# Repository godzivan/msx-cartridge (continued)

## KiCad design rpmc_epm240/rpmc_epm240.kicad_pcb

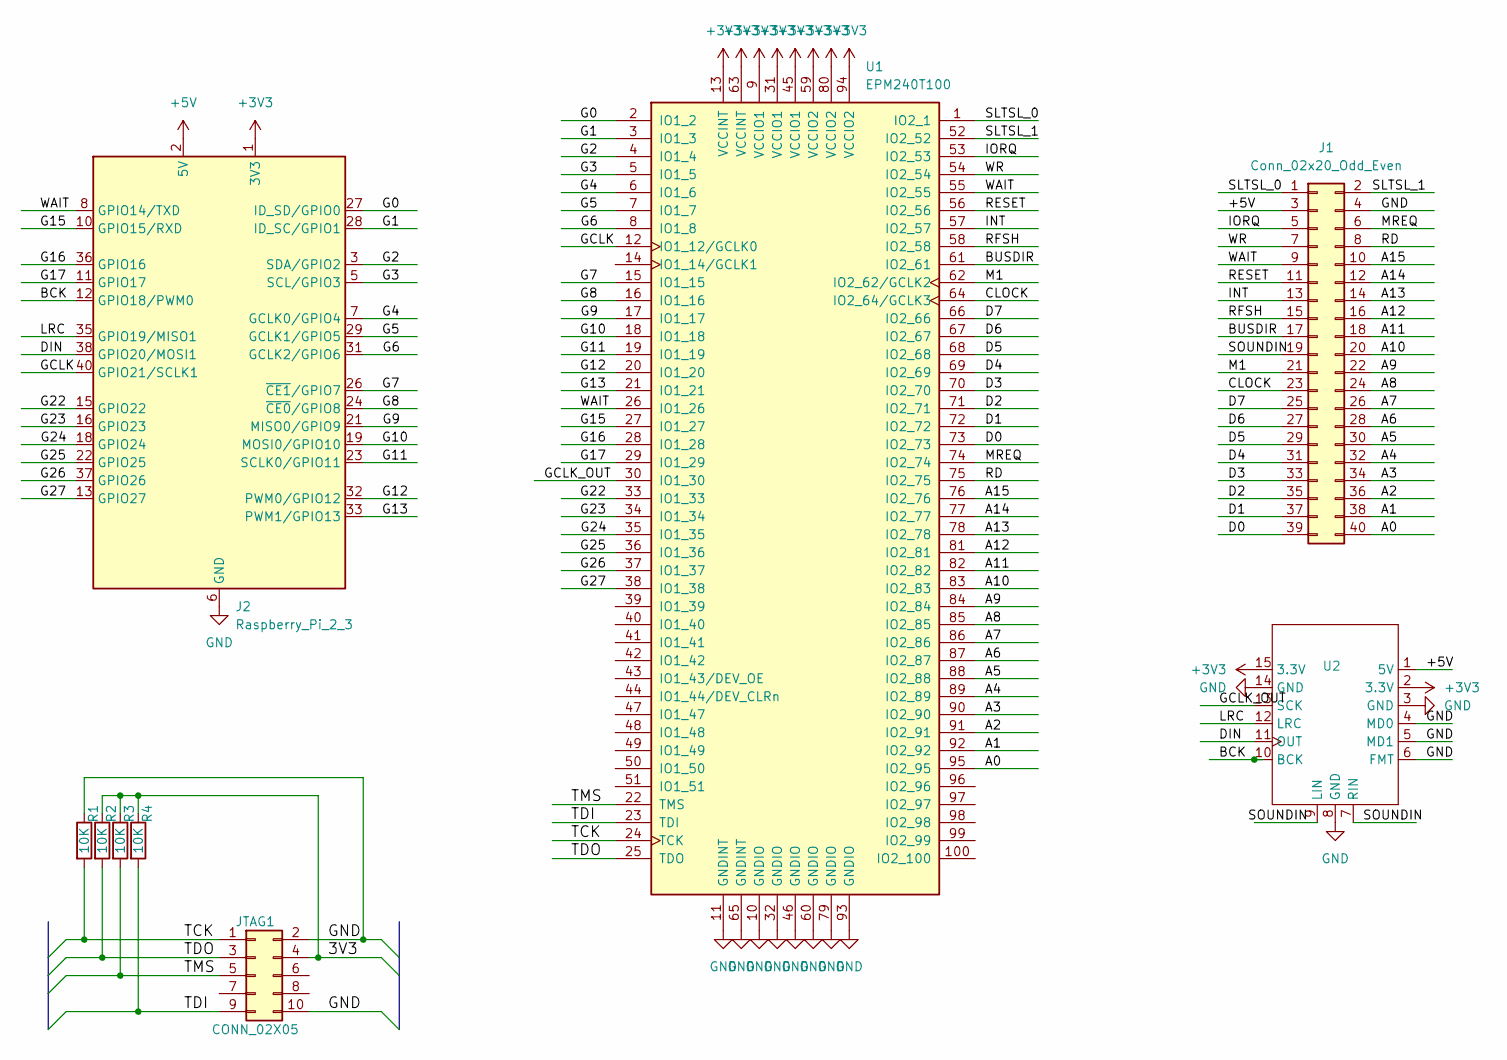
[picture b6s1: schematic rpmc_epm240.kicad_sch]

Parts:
J1: Conn_02x20_Odd_Even; PinHeader_2x20_P2.54mm_Vertical
J2: Raspberry_Pi_2_3; PinHeader_2x20_P2.54mm_Vertical
JTAG1: CONN_02X05; PinHeader_2x05_P2.54mm_Vertical
R1, R2, R3, R4: 10K; R_0201_0603Metric_Pad0.64x0.40mm_HandSolder
U1: EPM240T100; LQFP-100_14x14mm_P0.5mm
U2: PCM1808_EVB

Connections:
+3V3: J2.1 (3V3), J2.17 (3V3), U1.9 (VCCIO1), U1.13 (VCCINT), U1.31 (VCCIO1), U1.45 (VCCIO1), U1.59 (VCCIO2), U1.63 (VCCINT), U1.80 (VCCIO2), U1.94 (VCCIO2), U2.2 (3.3V), U2.15 (3.3V)
+5V: J1.3, J2.2 (5V), J2.4 (5V), U2.1 (5V)
/3V3: JTAG1.4, R2.1, R3.1, R4.1
/A0: J1.40, U1.95 (IO2_95)
/A1: J1.38, U1.92 (IO2_92)
/A2: J1.36, U1.91 (IO2_91)
/A3: J1.34, U1.90 (IO2_90)
/A4: J1.32, U1.89 (IO2_89)
/A5: J1.30, U1.88 (IO2_88)
/A6: J1.28, U1.87 (IO2_87)
/A7: J1.26, U1.86 (IO2_86)
/A8: J1.24, U1.85 (IO2_85)
/A9: J1.22, U1.84 (IO2_84)
/A10: J1.20, U1.83 (IO2_83)
/A11: J1.18, U1.82 (IO2_82)
/A12: J1.16, U1.81 (IO2_81)
/A13: J1.14, U1.78 (IO2_78)
/A14: J1.12, U1.77 (IO2_77)
/A15: J1.10, U1.76 (IO2_76)
/BCK: J2.12 (GPIO18/PWM0), U2.10 (BCK)
/BUSDIR: J1.17, U1.61 (IO2_61)
/CLOCK: J1.23, U1.64 (IO2_64/GCLK3)
/D0: J1.39, U1.73 (IO2_73)
/D1: J1.37, U1.72 (IO2_72)
/D2: J1.35, U1.71 (IO2_71)
/D3: J1.33, U1.70 (IO2_70)
/D4: J1.31, U1.69 (IO2_69)
/D5: J1.29, U1.68 (IO2_68)
/D6: J1.27, U1.67 (IO2_67)
/D7: J1.25, U1.66 (IO2_66)
/DIN: J2.38 (GPIO20/MOSI1), U2.11 (OUT)
/G0: J2.27 (ID_SD/GPIO0), U1.2 (IO1_2)
/G1: J2.28 (ID_SC/GPIO1), U1.3 (IO1_3)
/G2: J2.3 (SDA/GPIO2), U1.4 (IO1_4)
/G3: J2.5 (SCL/GPIO3), U1.5 (IO1_5)
/G4: J2.7 (GCLK0/GPIO4), U1.6 (IO1_6)
/G5: J2.29 (GCLK1/GPIO5), U1.7 (IO1_7)
/G6: J2.31 (GCLK2/GPIO6), U1.8 (IO1_8)
/G7: J2.26 (~CE1/GPIO7), U1.15 (IO1_15)
/G8: J2.24 (~CE0/GPIO8), U1.16 (IO1_16)
/G9: J2.21 (MISO0/GPIO9), U1.17 (IO1_17)
/G10: J2.19 (MOSI0/GPIO10), U1.18 (IO1_18)
/G11: J2.23 (SCLK0/GPIO11), U1.19 (IO1_19)
/G12: J2.32 (PWM0/GPIO12), U1.20 (IO1_20)
/G13: J2.33 (PWM1/GPIO13), U1.21 (IO1_21)
/G15: J2.10 (GPIO15/RXD), U1.27 (IO1_27)
/G16: J2.36 (GPIO16), U1.28 (IO1_28)
/G17: J2.11 (GPIO17), U1.29 (IO1_29)
/G22: J2.15 (GPIO22), U1.33 (IO1_33)
/G23: J2.16 (GPIO23), U1.34 (IO1_34)
/G24: J2.18 (GPIO24), U1.35 (IO1_35)
/G25: J2.22 (GPIO25), U1.36 (IO1_36)
/G26: J2.37 (GPIO26), U1.37 (IO1_37)
/G27: J2.13 (GPIO27), U1.38 (IO1_38)
/GCLK: J2.40 (GPIO21/SCLK1), U1.12 (IO1_12/GCLK0)
/GCLK_OUT: U1.30 (IO1_30), U2.13 (SCK)
/INT: J1.13, U1.57 (IO2_57)
/IORQ: J1.5, U1.53 (IO2_53)
/LRC: J2.35 (GPIO19/MISO1), U2.12 (LRC)
/M1: J1.21, U1.62 (IO2_62/GCLK2)
/MREQ: J1.6, U1.74 (IO2_74)
/RD: J1.8, U1.75 (IO2_75)
/RESET: J1.11, U1.56 (IO2_56)
/RFSH: J1.15, U1.58 (IO2_58)
/SLTSL_0: J1.1, U1.1 (IO2_1)
/SLTSL_1: J1.2, U1.52 (IO2_52)
/SOUNDIN: J1.19, U2.7 (RIN), U2.9 (LIN)
/TCK: JTAG1.1, R1.2, U1.24 (TCK)
/TDI: JTAG1.9, R4.2, U1.23 (TDI)
/TDO: JTAG1.3, R2.2, U1.25 (TDO)
/TMS: JTAG1.5, R3.2, U1.22 (TMS)
/WAIT: J1.9, J2.8 (GPIO14/TXD), U1.26 (IO1_26), U1.55 (IO2_55)
/WR: J1.7, U1.54 (IO2_54)
GND: J1.4, J2.6 (GND), J2.9 (GND), J2.14 (GND), J2.20 (GND), J2.25 (GND), J2.30 (GND), J2.34 (GND), J2.39 (GND), JTAG1.2, JTAG1.10, R1.1, U1.10 (GNDIO), U1.11 (GNDINT), U1.32 (GNDIO), U1.46 (GNDIO), U1.60 (GNDIO), U1.65 (GNDINT), U1.79 (GNDIO), U1.93 (GNDIO), U2.3 (GND), U2.4 (MD0), U2.5 (MD1), U2.6 (FMT), U2.8 (GND), U2.14 (GND)

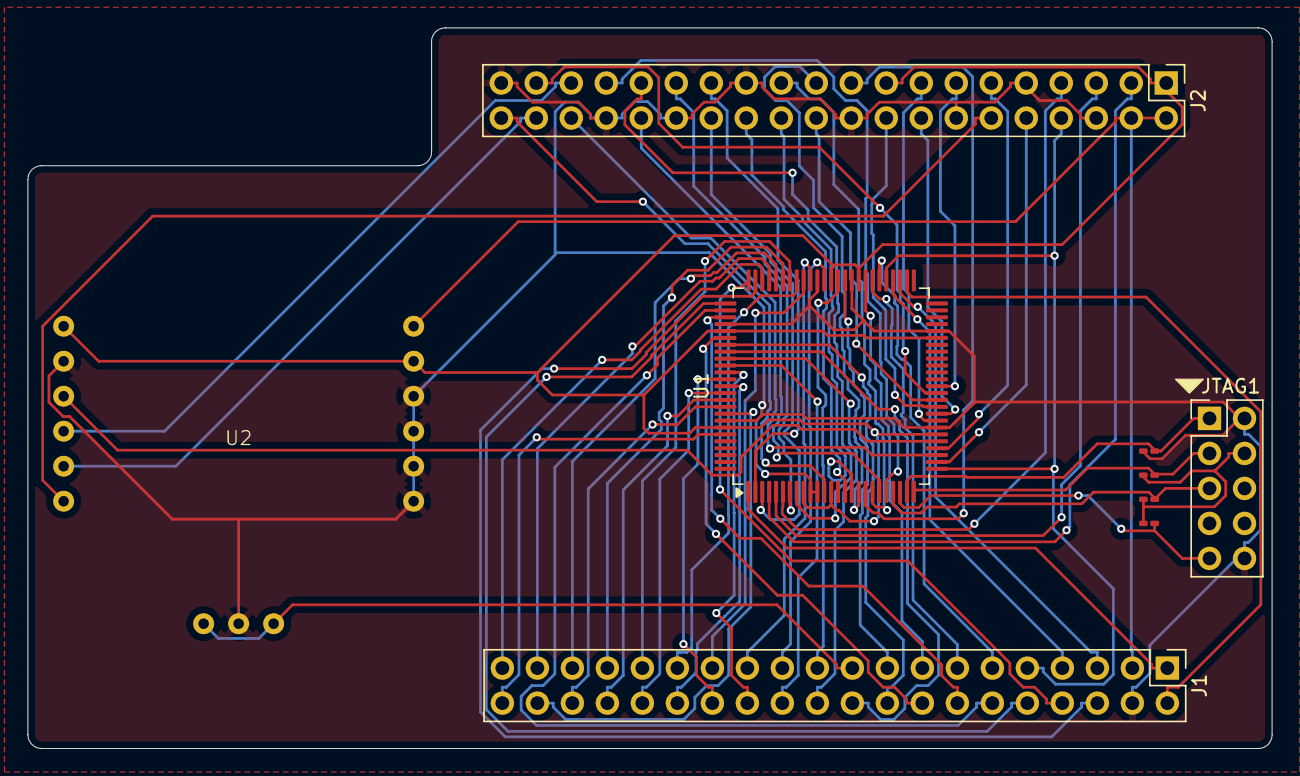
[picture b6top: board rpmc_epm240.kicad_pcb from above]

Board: 2 copper layers, 90.3 x 52.3 mm, 9 parts (0 on the bottom side), 74 nets.

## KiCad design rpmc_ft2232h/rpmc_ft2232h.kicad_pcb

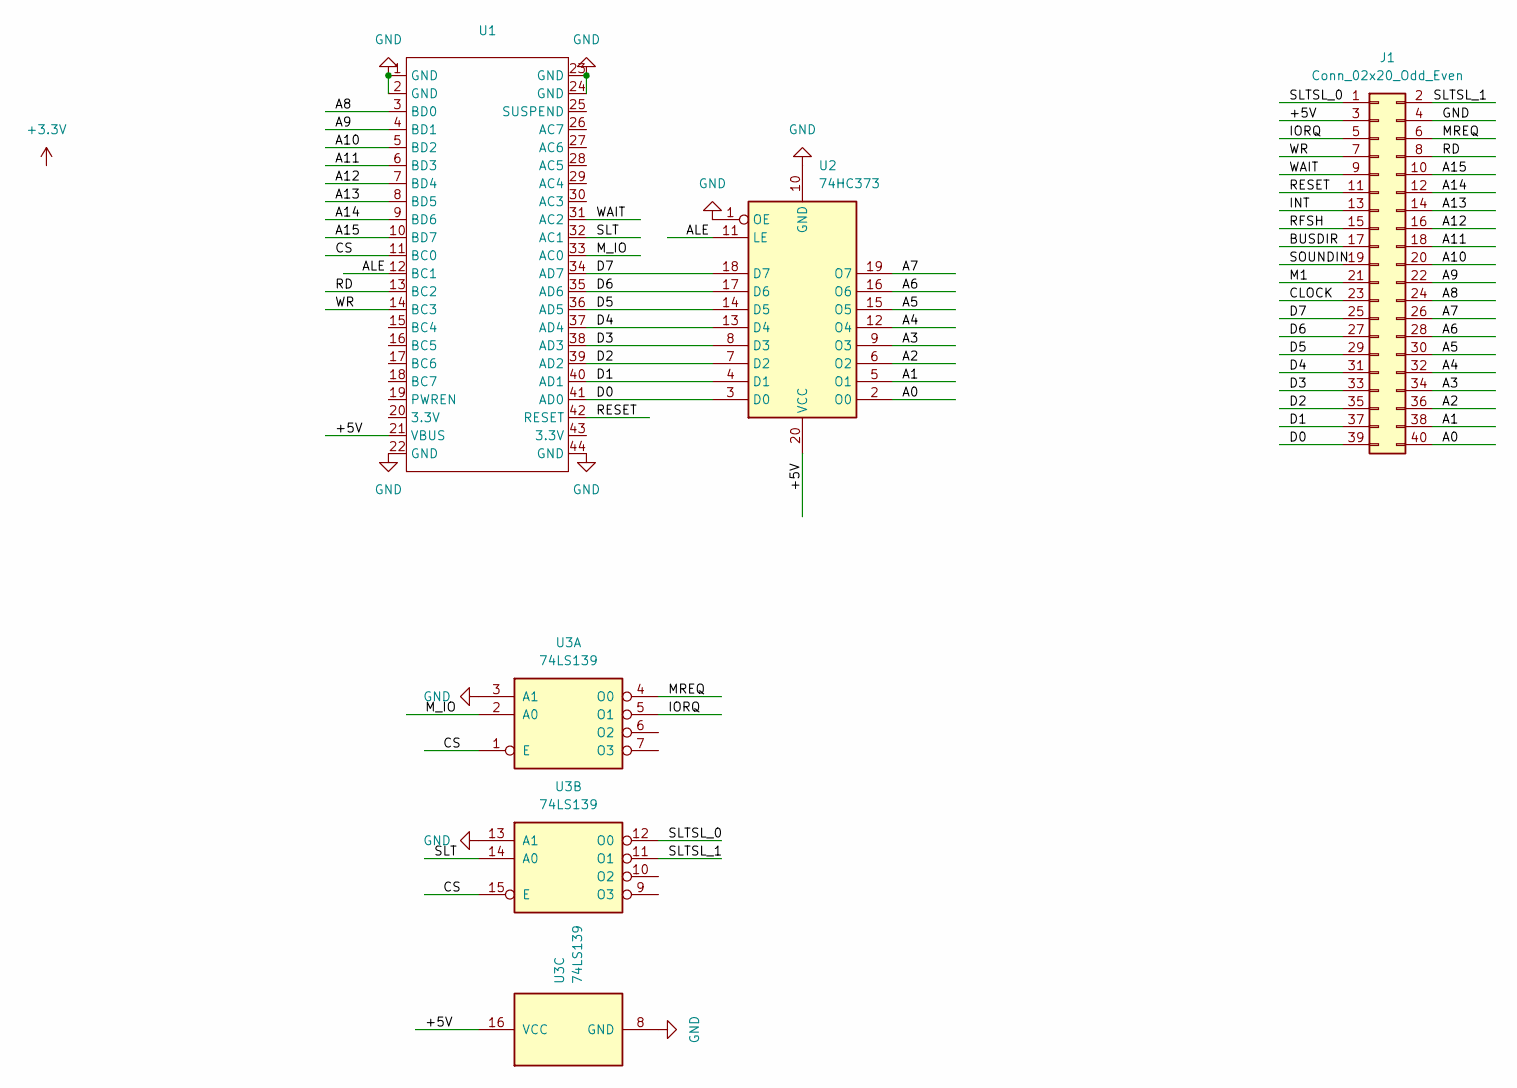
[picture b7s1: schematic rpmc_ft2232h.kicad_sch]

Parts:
J1: Conn_02x20_Odd_Even; PinHeader_2x20_P2.54mm_Vertical
U1: FT2232H_EVB
U2: 74HC373; SOIC-20_L13.0-W7.6-P1.27-LS10.3-BL
U3: 74LS139; SOIC-16_L10.8-W4.5-P1.27-LS6.8-BL

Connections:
/+5V: J1.3, U1.21 (VBUS), U2.20 (VCC), U3.16 (VCC)
/A0: J1.40, U2.2 (O0)
/A1: J1.38, U2.5 (O1)
/A2: J1.36, U2.6 (O2)
/A3: J1.34, U2.9 (O3)
/A4: J1.32, U2.12 (O4)
/A5: J1.30, U2.15 (O5)
/A6: J1.28, U2.16 (O6)
/A7: J1.26, U2.19 (O7)
/A8: J1.24, U1.3 (BD0)
/A9: J1.22, U1.4 (BD1)
/A10: J1.20, U1.5 (BD2)
/A11: J1.18, U1.6 (BD3)
/A12: J1.16, U1.7 (BD4)
/A13: J1.14, U1.8 (BD5)
/A14: J1.12, U1.9 (BD6)
/A15: J1.10, U1.10 (BD7)
/ALE: U1.12 (BC1), U2.11 (LE)
/BUSDIR: J1.17
/CLOCK: J1.23
/CS: U1.11 (BC0), U3.1 (E), U3.15 (E)
/D0: J1.39, U1.41 (AD0), U2.3 (D0)
/D1: J1.37, U1.40 (AD1), U2.4 (D1)
/D2: J1.35, U1.39 (AD2), U2.7 (D2)
/D3: J1.33, U1.38 (AD3), U2.8 (D3)
/D4: J1.31, U1.37 (AD4), U2.13 (D4)
/D5: J1.29, U1.36 (AD5), U2.14 (D5)
/D6: J1.27, U1.35 (AD6), U2.17 (D6)
/D7: J1.25, U1.34 (AD7), U2.18 (D7)
/INT: J1.13
/IORQ: J1.5, U3.5 (O1)
/M1: J1.21
/MREQ: J1.6, U3.4 (O0)
/M_IO: U1.33 (AC0), U3.2 (A0)
/RD: J1.8, U1.13 (BC2)
/RESET: J1.11, U1.42 (RESET)
/RFSH: J1.15
/SLT: U1.32 (AC1), U3.14 (A0)
/SLTSL_0: J1.1, U3.12 (O0)
/SLTSL_1: J1.2, U3.11 (O1)
/SOUNDIN: J1.19
/WAIT: J1.9, U1.31 (AC2)
/WR: J1.7, U1.14 (BC3)
GND: J1.4, U1.1 (GND), U1.2 (GND), U1.22 (GND), U1.23 (GND), U1.24 (GND), U1.44 (GND), U2.1 (OE), U2.10 (GND), U3.3 (A1), U3.8 (GND), U3.13 (A1)

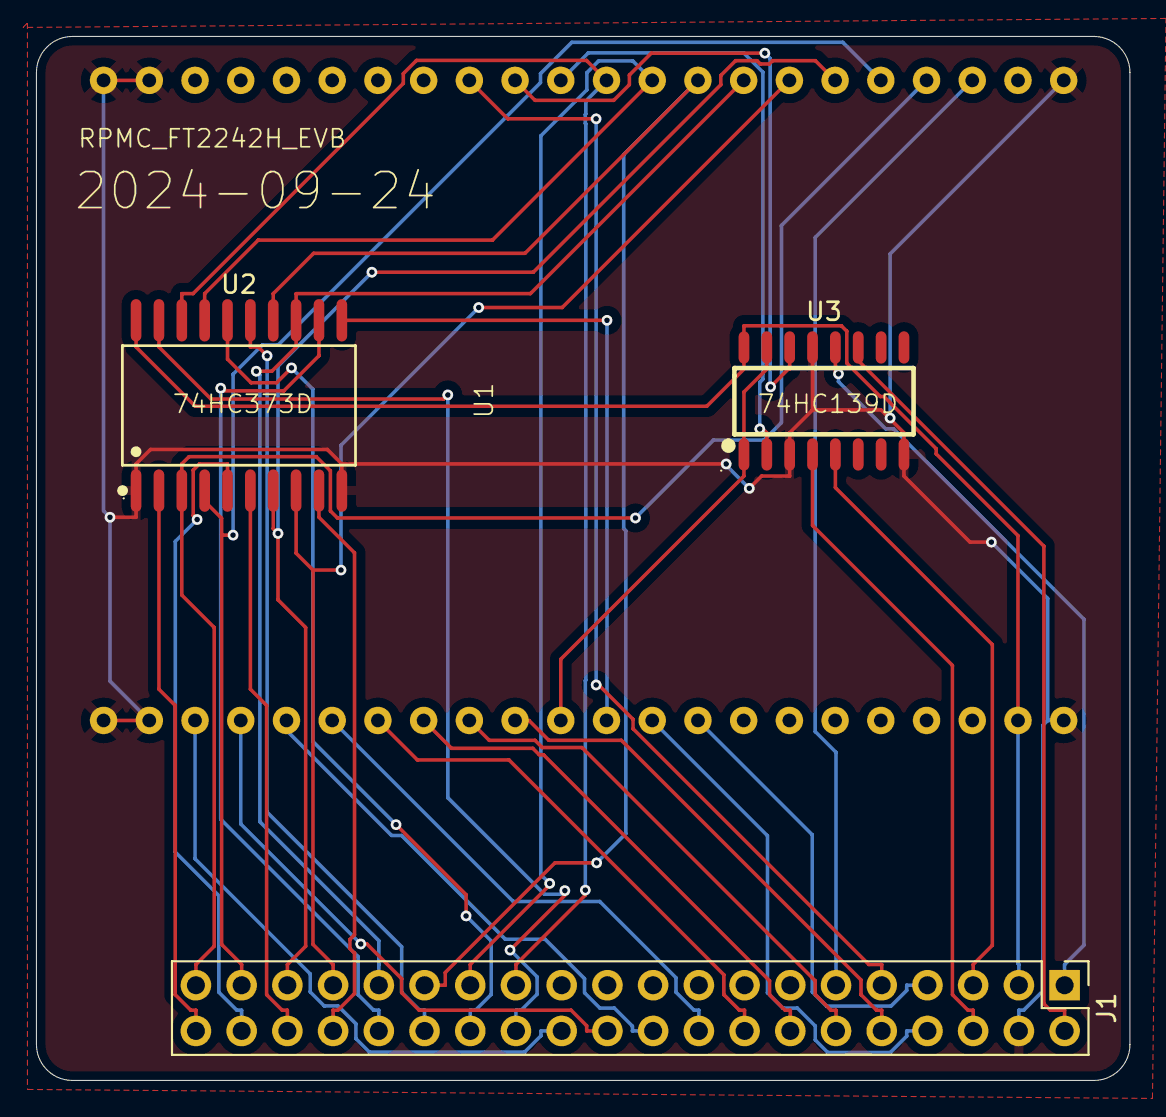
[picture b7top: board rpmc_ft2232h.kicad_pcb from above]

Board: 2 copper layers, 60.8 x 58.0 mm, 4 parts (0 on the bottom side), 38 nets.

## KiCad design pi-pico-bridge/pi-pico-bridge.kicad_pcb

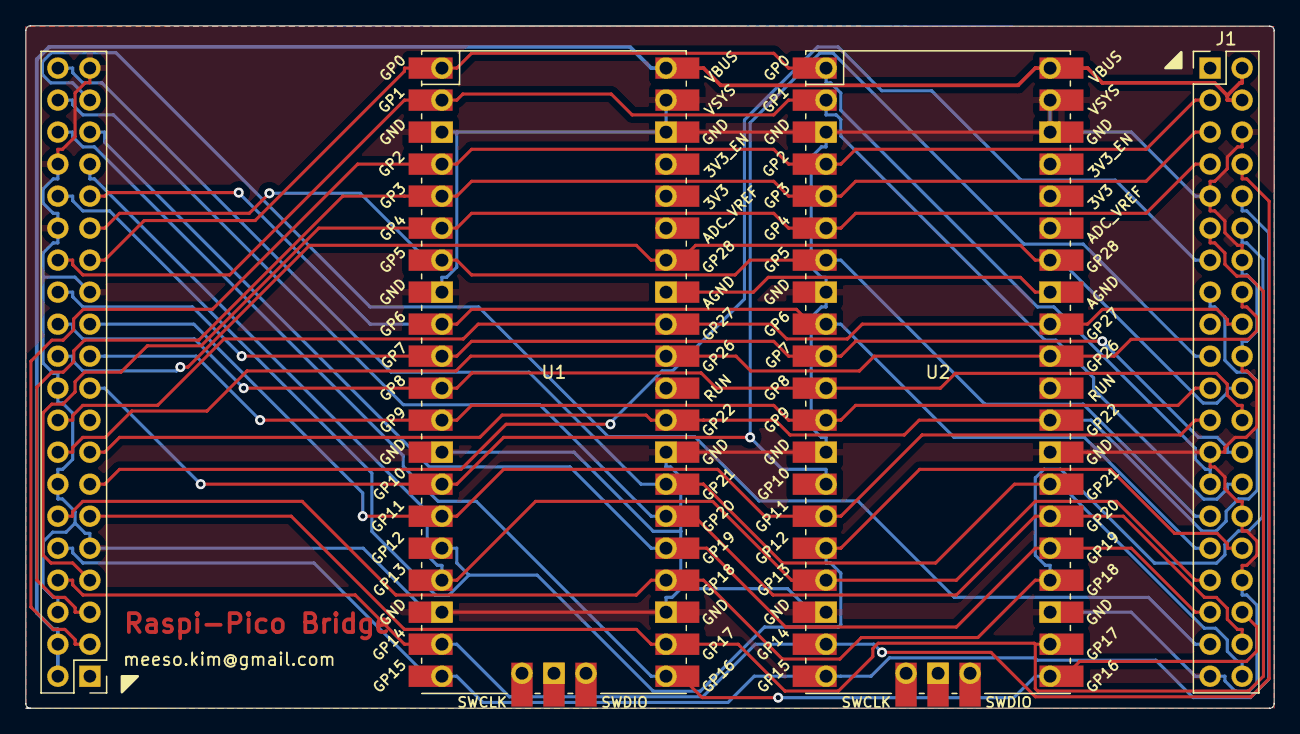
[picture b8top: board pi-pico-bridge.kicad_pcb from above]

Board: 2 copper layers, 99.1 x 54.2 mm, 4 parts (0 on the bottom side), 31 nets.

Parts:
J1, J2: Raspberry_Pi_2_3; PinHeader_2x20_P2.54mm_Vertical
U1, U2: Pico; RPi_Pico_SMD_TH_PinOut

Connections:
+5V: J1.2 (5V), J1.4 (5V), J2.2 (5V), J2.4 (5V), U1.40 (VBUS), U2.40 (VBUS)
/AGND: U1.33 (AGND), U2.33 (AGND)
/GP00: J1.27 (ID_SD/GPIO0), J2.27 (ID_SD/GPIO0), U1.1 (GPIO0), U2.1 (GPIO0)
/GP01: J1.28 (ID_SC/GPIO1), J2.28 (ID_SC/GPIO1), U1.2 (GPIO1), U2.2 (GPIO1)
/GP02: J1.3 (SDA/GPIO2), J2.3 (SDA/GPIO2), U1.4 (GPIO2), U2.4 (GPIO2)
/GP03: J1.5 (SCL/GPIO3), J2.5 (SCL/GPIO3), U1.5 (GPIO3), U2.5 (GPIO3)
/GP04: J1.7 (GCLK0/GPIO4), J2.7 (GCLK0/GPIO4), U1.6 (GPIO4), U2.6 (GPIO4)
/GP05: J1.29 (GCLK1/GPIO5), J2.29 (GCLK1/GPIO5), U1.7 (GPIO5), U2.7 (GPIO5)
/GP06: J1.31 (GCLK2/GPIO6), J2.31 (GCLK2/GPIO6), U1.9 (GPIO6), U2.9 (GPIO6)
/GP07: J1.26 (~CE1/GPIO7), J2.26 (~CE1/GPIO7), U1.10 (GPIO7), U2.10 (GPIO7)
/GP08: J1.24 (~CE0/GPIO8), J2.24 (~CE0/GPIO8), U1.11 (GPIO8), U2.11 (GPIO8)
/GP09: J1.21 (MISO0/GPIO9), J2.21 (MISO0/GPIO9), U1.12 (GPIO9), U2.12 (GPIO9)
/GP10: J1.19 (MOSI0/GPIO10), J2.19 (MOSI0/GPIO10), U1.14 (GPIO10), U2.14 (GPIO10)
/GP11: J1.23 (SCLK0/GPIO11), J2.23 (SCLK0/GPIO11), U1.15 (GPIO11), U2.15 (GPIO11)
/GP12: J1.32 (PWM0/GPIO12), J2.32 (PWM0/GPIO12), U1.16 (GPIO12), U2.16 (GPIO12)
/GP13: J1.33 (PWM1/GPIO13), J2.33 (PWM1/GPIO13), U1.17 (GPIO13), U2.17 (GPIO13)
/GP14: J1.8 (GPIO14/TXD), J2.8 (GPIO14/TXD), U1.19 (GPIO14), U2.19 (GPIO14)
/GP15: J1.10 (GPIO15/RXD), J2.10 (GPIO15/RXD), U1.20 (GPIO15), U2.20 (GPIO15)
/GP16: J1.36 (GPIO16), J2.36 (GPIO16), U1.21 (GPIO16), U2.21 (GPIO16)
/GP17: J1.11 (GPIO17), J2.11 (GPIO17), U1.22 (GPIO17), U2.22 (GPIO17)
/GP18: J1.12 (GPIO18/PWM0), J2.12 (GPIO18/PWM0), U1.24 (GPIO18), U2.24 (GPIO18)
/GP19: J1.35 (GPIO19/MISO1), J2.35 (GPIO19/MISO1), U1.25 (GPIO19), U2.25 (GPIO19)
/GP20: J1.38 (GPIO20/MOSI1), J2.38 (GPIO20/MOSI1), U1.26 (GPIO20), U2.26 (GPIO20)
/GP21: J1.40 (GPIO21/SCLK1), J2.40 (GPIO21/SCLK1), U1.27 (GPIO21), U2.27 (GPIO21)
/GP22: J1.15 (GPIO22), J2.15 (GPIO22), U1.29 (GPIO22), U2.29 (GPIO22)
/GP23: J1.16 (GPIO23), J2.16 (GPIO23), U1.31 (GPIO26_ADC0), U2.31 (GPIO26_ADC0)
/GP24: J1.18 (GPIO24), J2.18 (GPIO24), U1.32 (GPIO27_ADC1), U2.32 (GPIO27_ADC1)
/GP25: J1.22 (GPIO25), J2.22 (GPIO25), U1.34 (GPIO28_ADC2), U2.34 (GPIO28_ADC2)
/GP26: J1.37 (GPIO26), J2.37 (GPIO26)
/GP27: J1.13 (GPIO27), J2.13 (GPIO27)
GND: J1.6 (GND), J1.9 (GND), J1.14 (GND), J1.20 (GND), J1.25 (GND), J1.30 (GND), J1.34 (GND), J1.39 (GND), J2.6 (GND), J2.9 (GND), J2.14 (GND), J2.20 (GND), J2.25 (GND), J2.30 (GND), J2.34 (GND), J2.39 (GND), U1.3 (GND), U1.8 (GND), U1.13 (GND), U1.18 (GND), U1.23 (GND), U1.28 (GND), U1.38 (GND), U1.39 (VSYS), U2.3 (GND), U2.8 (GND), U2.13 (GND), U2.18 (GND), U2.23 (GND), U2.28 (GND), U2.38 (GND), U2.39 (VSYS)

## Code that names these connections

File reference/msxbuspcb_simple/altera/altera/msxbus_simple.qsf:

# -------------------------------------------------------------------------- #
#
# Copyright (C) 1991-2013 Altera Corporation
# Your use of Altera Corporation's design tools, logic functions 
# and other software and tools, and its AMPP partner logic 
# functions, and any output files from any of the foregoing 
# (including device programming or simulation files), and any 
# associated documentation or information are expressly subject 
# to the terms and conditions of the Altera Program License 
# Subscription Agreement, Altera MegaCore Function License 
# Agreement, or other applicable license agreement, including, 
# without limitation, that your use is for the sole purpose of 
# programming logic devices manufactured by Altera and sold by 
# Altera or its authorized distributors.  Please refer to the 
# applicable agreement for further details.
#
# -------------------------------------------------------------------------- #
#
# Quartus II 64-Bit
# Version 13.1.0 Build 162 10/23/2013 SJ Web Edition
# Date created = 19:35:26  January 29, 2017
#
# -------------------------------------------------------------------------- #
#
# Notes:
#
# 1) The default values for assignments are stored in the file:
#		msxbus_simple_assignment_defaults.qdf
#    If this file doesn't exist, see file:
#		assignment_defaults.qdf
#
# 2) Altera recommends that you do not modify this file. This
#    file is updated automatically by the Quartus II software
#    and any changes you make may be lost or overwritten.
#
# -------------------------------------------------------------------------- #


set_global_assignment -name FAMILY "MAX II"
set_global_assignment -name DEVICE EPM240T100C5
set_global_assignment -name TOP_LEVEL_ENTITY msxbus_simple
set_global_assignment -name ORIGINAL_QUARTUS_VERSION 13.1
set_global_assignment -name PROJECT_CREATION_TIME_DATE "19:35:26  JANUARY 29, 2017"
set_global_assignment -name LAST_QUARTUS_VERSION 13.1
set_global_assignment -name PROJECT_OUTPUT_DIRECTORY output_files
set_global_assignment -name MIN_CORE_JUNCTION_TEMP 0
set_global_assignment -name MAX_CORE_JUNCTION_TEMP 85
set_global_assignment -name DEVICE_FILTER_PACKAGE TQFP
set_global_assignment -name DEVICE_FILTER_PIN_COUNT 100
set_global_assignment -name ERROR_CHECK_FREQUENCY_DIVISOR "-1"
set_global_assignment -name POWER_EXT_SUPPLY_VOLTAGE_TO_REGULATOR 3.3V
set_global_assignment -name STRATIX_DEVICE_IO_STANDARD "3.3-V LVTTL"
set_location_assignment PIN_54 -to ADDR[15]
set_location_assignment PIN_47 -to ADDR[14]
set_location_assignment PIN_44 -to ADDR[13]
set_location_assignment PIN_49 -to ADDR[12]
set_location_assignment PIN_53 -to ADDR[11]
set_location_assignment PIN_52 -to ADDR[10]
set_location_assignment PIN_55 -to ADDR[9]
set_location_assignment PIN_48 -to ADDR[8]
set_location_assignment PIN_51 -to ADDR[7]
set_location_assignment PIN_50 -to ADDR[6]
set_location_assignment PIN_39 -to ADDR[5]
set_location_assignment PIN_38 -to ADDR[4]
set_location_assignment PIN_41 -to ADDR[3]
set_location_assignment PIN_40 -to ADDR[2]
set_location_assignment PIN_43 -to ADDR[1]
set_location_assignment PIN_42 -to ADDR[0]
set_location_assignment PIN_58 -to WR
set_location_assignment PIN_83 -to BUSDIR
set_location_assignment PIN_64 -to CLK
set_location_assignment PIN_72 -to CS1
set_location_assignment PIN_71 -to CS2
set_location_assignment PIN_70 -to CS12
set_location_assignment PIN_29 -to DATA[7]
set_location_assignment PIN_28 -to DATA[6]
set_location_assignment PIN_33 -to DATA[5]
set_location_assignment PIN_30 -to DATA[4]
set_location_assignment PIN_35 -to DATA[3]
set_location_assignment PIN_34 -to DATA[2]
set_location_assignment PIN_37 -to DATA[1]
set_location_assignment PIN_36 -to DATA[0]
set_location_assignment PIN_67 -to INT
set_location_assignment PIN_62 -to IORQ
set_location_assignment PIN_27 -to MCLK
set_location_assignment PIN_82 -to MD[15]
set_location_assignment PIN_81 -to MD[14]
set_location_assignment PIN_8 -to MD[13]
set_location_assignment PIN_7 -to MD[12]
set_location_assignment PIN_98 -to MD[11]
set_location_assignment PIN_92 -to MD[10]
set_location_assignment PIN_96 -to MD[9]
set_location_assignment PIN_99 -to MD[8]
set_location_assignment PIN_1 -to MD[7]
set_location_assignment PIN_6 -to MD[6]
set_location_assignment PIN_4 -to MD[5]
set_location_assignment PIN_78 -to MD[4]
set_location_assignment PIN_76 -to MD[3]
set_location_assignment PIN_77 -to MD[2]
set_location_assignment PIN_3 -to MD[1]
set_location_assignment PIN_2 -to MD[0]
set_location_assignment PIN_16 -to MODE[1]
set_location_assignment PIN_91 -to MODE[0]
set_location_assignment PIN_61 -to MREQ
set_location_assignment PIN_57 -to RD
set_location_assignment PIN_97 -to READY
set_location_assignment PIN_56 -to RESET
set_location_assignment PIN_73 -to SLTSL[1]
set_location_assignment PIN_69 -to SLTSL[0]
set_location_assignment PIN_21 -to SW[1]
set_location_assignment PIN_20 -to SW[0]
set_location_assignment PIN_26 -to SWOUT
set_location_assignment PIN_68 -to WAIT
set_location_assignment PIN_15 -to MD[16]
set_location_assignment PIN_84 -to MD[17]
set_location_assignment PIN_85 -to MD[18]
set_location_assignment PIN_14 -to MD[19]
set_location_assignment PIN_17 -to MD[20]
set_instance_assignment -name WEAK_PULL_UP_RESISTOR ON -to DATA
set_instance_assignment -name CURRENT_STRENGTH_NEW "MINIMUM CURRENT" -to DATA
set_instance_assignment -name IO_STANDARD "3.3-V LVTTL" -to DATA
set_instance_assignment -name ENABLE_BUS_HOLD_CIRCUITRY OFF -to DATA
set_instance_assignment -name CURRENT_STRENGTH_NEW 4MA -to ADDR
set_instance_assignment -name WEAK_PULL_UP_RESISTOR ON -to CS1
set_instance_assignment -name WEAK_PULL_UP_RESISTOR ON -to CS2
set_instance_assignment -name WEAK_PULL_UP_RESISTOR ON -to CS12
set_instance_assignment -name WEAK_PULL_UP_RESISTOR ON -to SLTSL
set_instance_assignment -name WEAK_PULL_UP_RESISTOR ON -to RD
set_instance_assignment -name WEAK_PULL_UP_RESISTOR ON -to WR
set_instance_assignment -name WEAK_PULL_UP_RESISTOR ON -to IORQ
set_instance_assignment -name WEAK_PULL_UP_RESISTOR ON -to MREQ
set_instance_assignment -name FAST_OUTPUT_REGISTER ON -to SLTSL
set_instance_assignment -name FAST_OUTPUT_ENABLE_REGISTER ON -to RD
set_instance_assignment -name FAST_OUTPUT_ENABLE_REGISTER ON -to IORQ
set_instance_assignment -name WEAK_PULL_UP_RESISTOR ON -to ADDR
set_instance_assignment -name AUTO_GLOBAL_CLOCK ON -to CLK
set_instance_assignment -name FAST_INPUT_REGISTER ON -to DATA
set_instance_assignment -name FAST_OUTPUT_REGISTER ON -to ADDR
set_instance_assignment -name FAST_OUTPUT_REGISTER ON -to MREQ
set_instance_assignment -name IO_STANDARD "3.3-V LVCMOS" -to ADDR
set_instance_assignment -name IO_STANDARD "3.3-V LVCMOS" -to WR
set_instance_assignment -name CURRENT_STRENGTH_NEW 4MA -to WR
set_instance_assignment -name WEAK_PULL_UP_RESISTOR ON -to WAIT
set_location_assignment PIN_88 -to PSW0
set_location_assignment PIN_89 -to PSW1
set_instance_assignment -name CURRENT_STRENGTH_NEW "MAXIMUM CURRENT" -to BUSDIR
set_instance_assignment -name CURRENT_STRENGTH_NEW "MINIMUM CURRENT" -to CLK
set_instance_assignment -name CURRENT_STRENGTH_NEW "MINIMUM CURRENT" -to CS1
set_instance_assignment -name CURRENT_STRENGTH_NEW "MINIMUM CURRENT" -to CS2
set_instance_assignment -name CURRENT_STRENGTH_NEW "MINIMUM CURRENT" -to CS12
set_instance_assignment -name IO_STANDARD "3.3-V LVCMOS" -to IORQ
set_instance_assignment -name CURRENT_STRENGTH_NEW 4MA -to IORQ
set_instance_assignment -name IO_STANDARD "3.3-V LVCMOS" -to INT
set_instance_assignment -name CURRENT_STRENGTH_NEW 4MA -to INT
set_instance_assignment -name IO_STANDARD "3.3-V LVCMOS" -to RD
set_instance_assignment -name CURRENT_STRENGTH_NEW 4MA -to RD
set_global_assignment -name VHDL_FILE sram_controller.vhd
set_global_assignment -name VERILOG_FILE msxbus_simple.v
set_instance_assignment -name FAST_OUTPUT_ENABLE_REGISTER ON -to WR

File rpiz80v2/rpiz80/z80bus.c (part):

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 
// I/O access
volatile unsigned *gpio;
volatile unsigned *gpio10;
volatile unsigned *gpio7;
volatile unsigned *gpio13;
volatile unsigned *gpio1;
 
 
// GPIO setup macros. Always use INP_GPIO(x) before using OUT_GPIO(x) or SET_GPIO_ALT(x,y)
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#define OUT_GPIO(g) *(gpio+((g)/10)) |=  (1<<(((g)%10)*3))
#define SET_GPIO_ALT(g,a) *(gpio+(((g)/10))) |= (((a)<=3?(a)+4:(a)==4?3:2)<<(((g)%10)*3))
 
#define GPIO_SET *(gpio7)  // sets   bits which are 1 ignores bits which are 0
#define GPIO_CLR *(gpio10) // clears bits which are 1 ignores bits which are 0
 
#define GET_GPIO(g) (*(gpio13)&(1<<g)) // 0 if LOW, (1<<g) if HIGH
#define GPIO (*(gpio13))
 
#define GPIO_PULL *(gpio+37) // Pull up/pull down
#define GPIO_PULLCLK0 *(gpio+38) // Pull up/pull down clock
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	OUT_GPIO(MD06_PIN);
	OUT_GPIO(MD07_PIN);
#else
	*(gpio1) &= 0x0924927f;
	*(gpio1) |= 0x09249240;
	GPIO_SET = 0xff << MD00_PIN;	
#endif	
}
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	GPIO_CLR = SPI_SCLK; if (cs12)	GPIO_SET = SPI_MOSI; else GPIO_CLR = SPI_MOSI; GPIO_SET = SPI_SCLK;
	GPIO_CLR = SPI_SCLK; if (cs1)	GPIO_SET = SPI_MOSI; else GPIO_CLR = SPI_MOSI; GPIO_SET = SPI_SCLK;
	GPIO_CLR = SPI_SCLK; if (cs2)	GPIO_SET = SPI_MOSI; else GPIO_CLR = SPI_MOSI; GPIO_SET = SPI_SCLK;
	GPIO_CLR = SPI_SCLK; if (mreq)	GPIO_SET = SPI_MOSI; else GPIO_CLR = SPI_MOSI; GPIO_SET = SPI_SCLK;
	GPIO_CLR = SPI_SCLK; if (!mreq)	GPIO_SET = SPI_MOSI; else GPIO_CLR = SPI_MOSI; GPIO_SET = SPI_SCLK;
	GPIO_CLR = SPI_SCLK; if (rd)	GPIO_SET = SPI_MOSI; else GPIO_CLR = SPI_MOSI; GPIO_SET = SPI_SCLK;
	GPIO_CLR = SPI_SCLK; if (!rd)	GPIO_SET = SPI_MOSI; else GPIO_CLR = SPI_MOSI; GPIO_SET = SPI_SCLK;
	GPIO_CLR = SPI_SCLK; if (slt1 != 1)	GPIO_SET = SPI_MOSI; else GPIO_CLR = SPI_MOSI; GPIO_SET = SPI_SCLK;	
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 
   // Always use volatile pointer!
   gpio = (volatile unsigned *)gpio_map;
   gpio10 = gpio+10;
   gpio7 = gpio+7;
   gpio13 = gpio+13;
   gpio1 = gpio+1;
   
} // setup_io

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
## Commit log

2016-02-18 msxslot update
2016-02-19 arduino source for msx slot
2016-03-08 add feature with Altera CPLD EMP240
2016-03-09 msxbus PCB
2016-03-09 msxbus update
2016-03-13 update for RPMC
2016-03-14 route for pcb
2016-03-14 simple PCB added
2016-03-15 pcb update by usning EMP240 board
2016-03-16 RPMC slot update for CPLD simple development board
2016-03-17 capacitors added
2016-03-18 gbr file gererated
2016-03-20 epm240 12mm to 14mm
2016-04-10 update for pinout
2016-04-17 update for msxbus
2016-12-20 sync notepc and desktop
2016-12-20 schematic update
2016-12-21 RMPC msxbus update
2016-12-22 pcb edge update
2016-12-22 finshing
2016-12-23 update for better
2016-12-27 improved for pcb layout
2016-12-28 routing update
2017-01-08 big update msxrampack, msxbuspcb_simple for many
2017-02-05 RPMC CPLD programming update
2017-03-05 update for Verilog
2017-03-05 update of qsf
2017-03-07 different implementation
2017-03-12 modified for rom
2017-03-13 new version of Verilog for MSXBUS
2017-04-06 SRAM controller
2017-04-09 update for adopting sram_controller
2017-04-13 interface
2017-04-16 modified verilog for msxslot
2017-04-17 small modification for timing
2017-04-19 latest read perfect verilog for msxbus
2017-12-25 RPMC and RPSPC updated
2017-12-26 RPMC V3 RPSPC update
2017-12-27 rpmcv4 updated
2017-12-27 rpmcv4 renamed
2017-12-27 rpmcv4 updated for footprint of 74HC245
2017-12-27 rpmcv4 updated by using 74HC373 instead of 74HC595
2017-12-28 small improvement
2017-12-28 1st version of RPMP
2017-12-28 update board for RPMP
2018-01-14 update for rpmcv1 and rpspc
2018-01-14 rpspc update
2018-01-15 improvement for RPMP feature
2018-01-16 modification for rpmcv4 and rpibox
2018-01-19 minor update for rpspc, rpmcv4, rpmpv1
2018-01-22 clean up for all works
2018-01-29 minor update for rpibox v2
2018-02-12 RPMP V2 added
2018-02-22 RPMP V2 updated
2018-02-23 logic update for better control
2018-02-25 address injuection feature
2018-02-27 apple extension bus added
2018-03-06 modification for address line
2018-03-07 apple extension card revised
2018-03-07 software for RPMC V0.5
2018-03-13 RPMP V4 made
2018-03-20 update for RPMP V3
2018-03-22 Ras Apple II
2018-03-25 update for RPIZ80, RPIAPPLE, RPMSXP
2018-03-25 update of jtagboard
2018-03-26 update of RPMP v3 CPLD
2018-03-26 MOS 8502 test board
2018-03-26 jtag update
2018-03-26 update of 6502
2018-03-27 update for PCB order
2018-03-27 minor update for PCB order
2018-03-28 PCB files for order
2018-03-28 revised rpmpv3, rpmpv4
2018-04-16 rpmpv3 altera update
2018-04-16 rpmpv3 update
2018-04-17 global clock
2018-04-23 RPMP V6 created
2018-04-23 RPMP V6 updated and 74LVC4254A added
2018-04-23 RPMP V6 minor update
2018-04-24 RPMP V6 or gate (74HC32) to and gate (74HC08)
2018-04-24 RPMP V6 update
2018-04-25 RpiSPC V4 zero/2/3 support
2018-04-29 RPMC V5 created
2018-04-30 RPMP V5 and RPIZ80 V2 added
2018-04-30 PRMC V5 and RPIAPPLE V1 updated
2018-05-01 SPC/APPLE/RPMC/RPMP updated for PCB order
2018-05-01 schematics pdf added
2018-05-03 updates for orders
2018-05-07 minor updates
2018-05-07 TTL library added
2018-05-09 RPMC V6 added
2018-05-27 new board for RPMP
2018-05-29 kernel module for RPMP
2018-06-24 update for 74LVC2425 package
2018-06-25 dat_dir logic update for RPMPV8
2018-06-26 RPMPV8 updated
2018-06-27 PCB ordered RPMPV8, RPMCV8, RPISPCV5
2018-07-09 port decription added
2018-07-16 neo cart
2018-08-12 rpmpv9 added
2018-08-16 new boards
2018-08-23 RPMC V9 for real-like MSX machine
2018-08-24 schematic update or RPMC V8
2018-08-27 neo cart v1 final schematic
2018-10-30 lastest update
2018-11-13 RP-MTE V1
2019-01-01 RPMC V2019-1 added
2019-01-01 unnecessary referece removed
2019-02-13 many changes
2019-03-18 RPMP V11 revised at 2019.2
2019-03-25 prmpv12
2020-01-14 major updates for PCB
2020-02-27 rpmpv16 added
2020-02-28 update for new kicad but not perfect
2020-03-16 add new symbol
2020-03-17 new components
2020-03-17 new board with lichee pi nano
2020-03-23 new RPMP with PT8111
2020-03-24 lichee pi nano pcb modified
2020-03-25 rpmpv18 for sipeed m1w
2020-03-26 sipeed m1 module
2020-03-27 RPMP with sipeed m1w
2020-03-30 updates for K210/F1C100S
2020-04-05 updated for kicad
2020-04-07 updated for new PCB order
2020-04-26 rpmpv15-2 updated
2020-05-19 more test pcb
2020-05-19 new board for test
2020-05-25 updated for test
2023-03-01 rpispcv2/rpspc-rescue.lib rpispcv2/rpspc.kicad_pcb rpispcv4/fp-lib-table rpispcv4/rpspc-rescue.lib rpispcv4/rpspc.kicad_pcb
2023-03-01 pi-pico-bridge/#auto_saved_files# pi-pico-bridge/_autosave-pi-pico-bridge.kicad_sch pi-pico-bridge/fp-info-cache pi-pico-bridge/pi-pico-bridge-backups/pi-pico-bridge-2023-02-25_220951.zip pi-pico-bri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
2024-09-18 libraries/2024-09-18_09-58-07.kicad_sym:Zone.Identifier libraries/ADS1118IDGSR_C55347.kicad_sym libraries/FT2232H.kicad_sym libraries/SN74HC139DR.kicad_sym libraries/SN74HC373DWR.kicad_sym libraries/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
2024-09-19 libraries/2024-09-18_09-58-07.kicad_sym:Zone.Identifier
2024-09-19 msxbuspcb_simple/reference/1.0x0.jpg msxbuspcb_simple/reference/450399616_898.jpg msxbuspcb_simple/reference/5047221428579373033.JPG msxbuspcb_simple/reference/5pcs-maxii-epm240-cpld-fpga-mini-develo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
2024-09-19 reference/arduino/include/rom.h reference/arduino/rom.h reference/arduino/sketch_feb11a.ino reference/msxbus/.qsys_edit/filters.xml reference/msxbus/.qsys_edit/layout.xml reference/msxbus/.qsys_edit/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
2024-09-19 universal_msxslot/universal_msxslot.kicad_pcb
2024-09-20 libraries/74HC373D,653.kicad_sym libraries/TXB0108PWR.kicad_sym libraries/footprint/SOIC-20_L13.0-W7.6-P1.27-LS10.3-BL.kicad_mod libraries/footprint/TSSOP-20_L6.5-W4.4-P0.65-LS6.4-BL.kicad_mod librar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
2024-09-23 libraries/PCM1808_EVB.kicad_mod libraries/footprint/PCM1808_EVB.kicad_mod libraries/footprint/msx-cartridge/libraries/packages3d/SOIC-20_L13.0-W7.6-P1.27-LS10.3-BL.step libraries/msx.pretty/Library.p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
2024-09-23 rpmc_epm240/rpmc_epm240-backups/rpmc_epm240-2024-09-23_004329.zip rpmc_epm240/rpmc_epm240.kicad_sch
2024-09-23 libraries/footprint/PCM1808_EVB.kicad_mod
2024-09-23 rpmc_epm240.kicad_pcb
2024-09-23 libraries/footprint/FT2232H_EVB.kicad_mod libraries/footprint/SOIC-16_L10.8-W4.5-P1.27-LS6.8-BL.kicad_mod libraries/footprint/SOIC-20_L13.0-W7.6-P1.27-LS10.3-BL.kicad_mod libraries/msx_slot.kicad_sym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
2024-09-24 universal_msxslot/fp-lib-table universal_msxslot/sym-lib-table
2024-09-24 rpmc_logics/fp-info-cache rpmc_logics/fp-lib-table rpmc_logics/rpmc_logics.kicad_pcb rpmc_logics/rpmc_logics.kicad_sch
2024-09-24 rpmc_ft2232h/rpmc_ft2232h.kicad_pcb rpmc_ft2232h/rpmc_ft2232h.kicad_sch
2024-09-26 epm240
2024-09-26 universal_msxcart
2024-09-26 epm240_msxcart
2024-09-26 epm240_msxcart/epm240_msxcart.kicad_pcb epm240_msxcart/epm240_msxcart.kicad_prl epm240_msxcart/epm240_msxcart.kicad_sch epm240_msxcart/fp-info-cache epm240_msxcart/freerouting.dsn epm240_msxcart/free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
2024-10-04 universal_msxslot/fp-info-cache universal_msxslot/fp-lib-table universal_msxslot/parts/PinSocket_2x20_P2.54mm_Vertical_SMD_DIP.kicad_mod universal_msxslot/parts/TSSOP-14_L5.0-W4.4-P0.65-LS6.4-BL.kica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
2024-10-04 universal_msxcart/universal_msxcart.kicad_pcb universal_msxcart/universal_msxcart.kicad_pro universal_msxcart/universal_msxcart.kicad_sch
2024-10-06 universal_msxcart.kicad_pro universal_msxcart.kicad_sch
2024-10-06 rpmc_epm240/rpmc_epm240.kicad_prl rpmc_logics/rpmc_logics.kicad_pcb rpmc_logics/rpmc_logics.kicad_prl rpmc_logics/rpmc_logics.kicad_sch universal_msxcart/universal_msxcart.kicad_pcb
2024-10-06 ../rpmc_epm240/rpmc_epm240-backups/rpmc_epm240-2024-09-23_010603.zip ../rpmc_epm240/rpmc_epm240.kicad_sch .DS_Store .gitignore fp-lib-table parts/FT2232H_EVB.kicad_mod parts/PCM1808_EVB.kicad_mod par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
2024-10-06 rpmp_epm240.kicad_pcb rpmp_epm240.kicad_prl rpmp_epm240.kicad_sch
2024-10-06 ../universal_msxcart/universal_msxcart.kicad_pcb ../universal_msxcart/universal_msxcart.kicad_prl
2025-03-05 Makefile altera/db/.cmp.kpt altera/db/logic_util_heursitic.dat altera/db/msxbus_simple.(0).cnf.cdb altera/db/msxbus_simple.(0).cnf.hdb altera/db/msxbus_simple.(1).cnf.cdb altera/db/msxbus_simple.(1).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
2025-03-05 msxbus_simple.qsf msxbus_simple.v
